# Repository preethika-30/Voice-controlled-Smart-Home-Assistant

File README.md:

# Hardware integration placeholder

Keep the original KiCad PCB/schematic files in the repository root.

When connecting the agent to the physical smart-home prototype, put the ESP32/relay communication code here and call it from `agent/smart_home_agent.py` through `control_device()`.

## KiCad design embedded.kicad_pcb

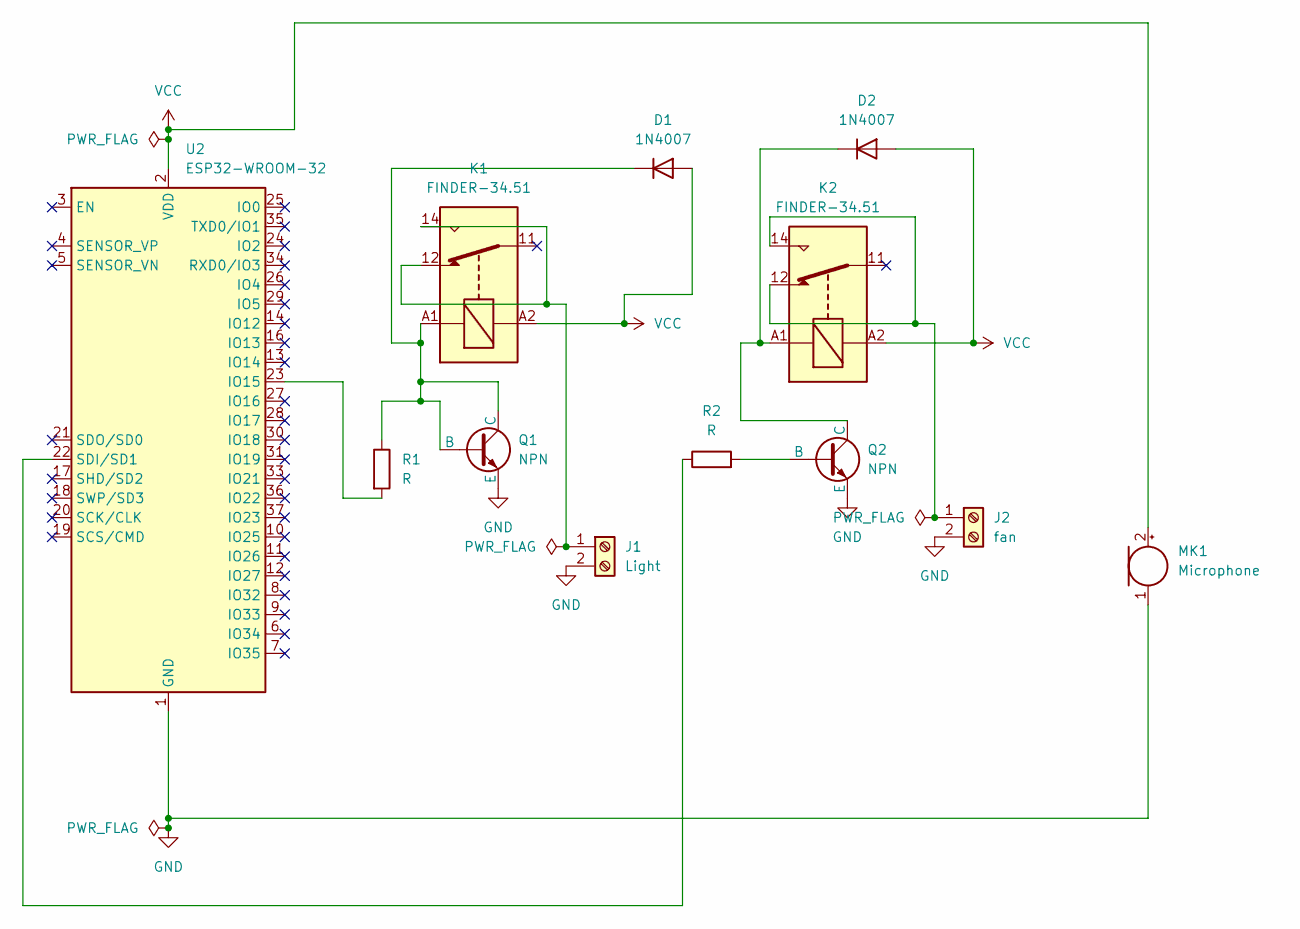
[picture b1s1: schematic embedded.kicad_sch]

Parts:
D1, D2: 1N4007; D_DO-41_SOD81_P10.16mm_Horizontal
J1: Light; D_DO-41_SOD81_P10.16mm_Horizontal
J2: fan; D_DO-41_SOD81_P10.16mm_Horizontal
K1, K2: FINDER-34.51; Relay_SPDT_Finder_34.51_Vertical
MK1: Microphone; SW_Cherry_MX_2.75u_Plate
Q1, Q2: NPN; Jack_XLR_Neutrik_NC3FAAV1-0_Vertical
R1, R2: R; R_0201_0603Metric_Pad0.64x0.40mm_HandSolder
U2: ESP32-WROOM-32

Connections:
GND: J1.2, J2.2, MK1.1 (-), Q1.3 (E), Q2.3 (E), U2.1 (GND), U2.15 (GND), U2.38 (GND), U2.39 (GND)
unnamed: D1.1 (K), K1.A1, Q1.1 (C), Q1.2 (B), R1.1
unnamed: D2.1 (K), K2.A1, Q2.1 (C)
unnamed: J1.1, K1.12, K1.14
unnamed: J2.1, K2.12, K2.14
unnamed: Q2.2 (B), R2.2
unnamed: R1.2, U2.23 (IO15)
unnamed: R2.1, U2.22 (SDI/SD1)
VCC: D1.2 (A), D2.2 (A), K1.A2, K2.A2, MK1.2 (+), U2.2 (VDD)

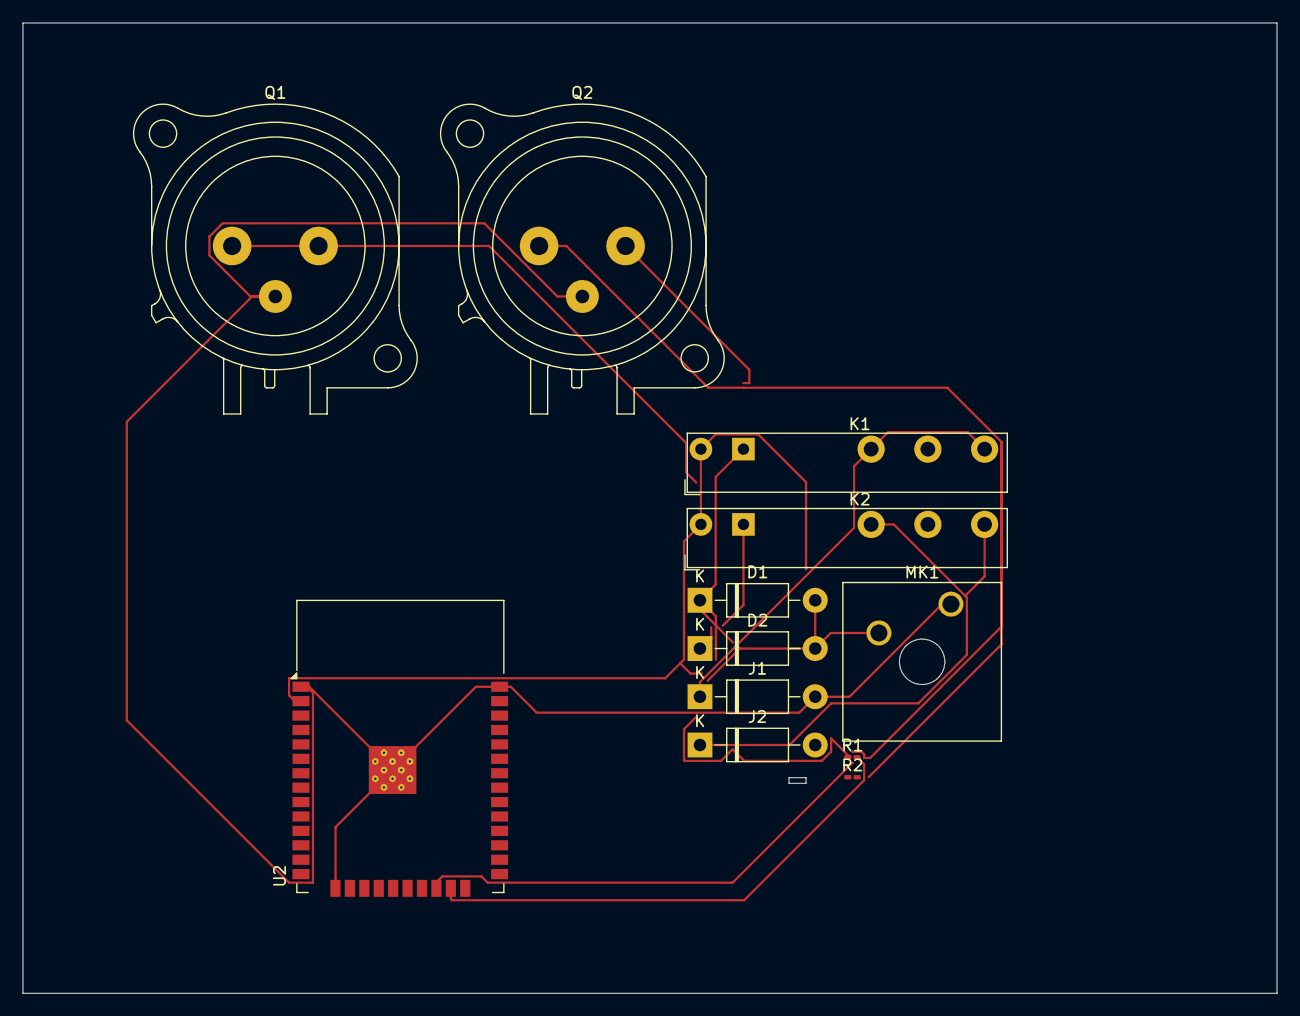
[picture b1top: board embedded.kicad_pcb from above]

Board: 2 copper layers, 110.5 x 85.5 mm, 12 parts (0 on the bottom side), 9 nets.
